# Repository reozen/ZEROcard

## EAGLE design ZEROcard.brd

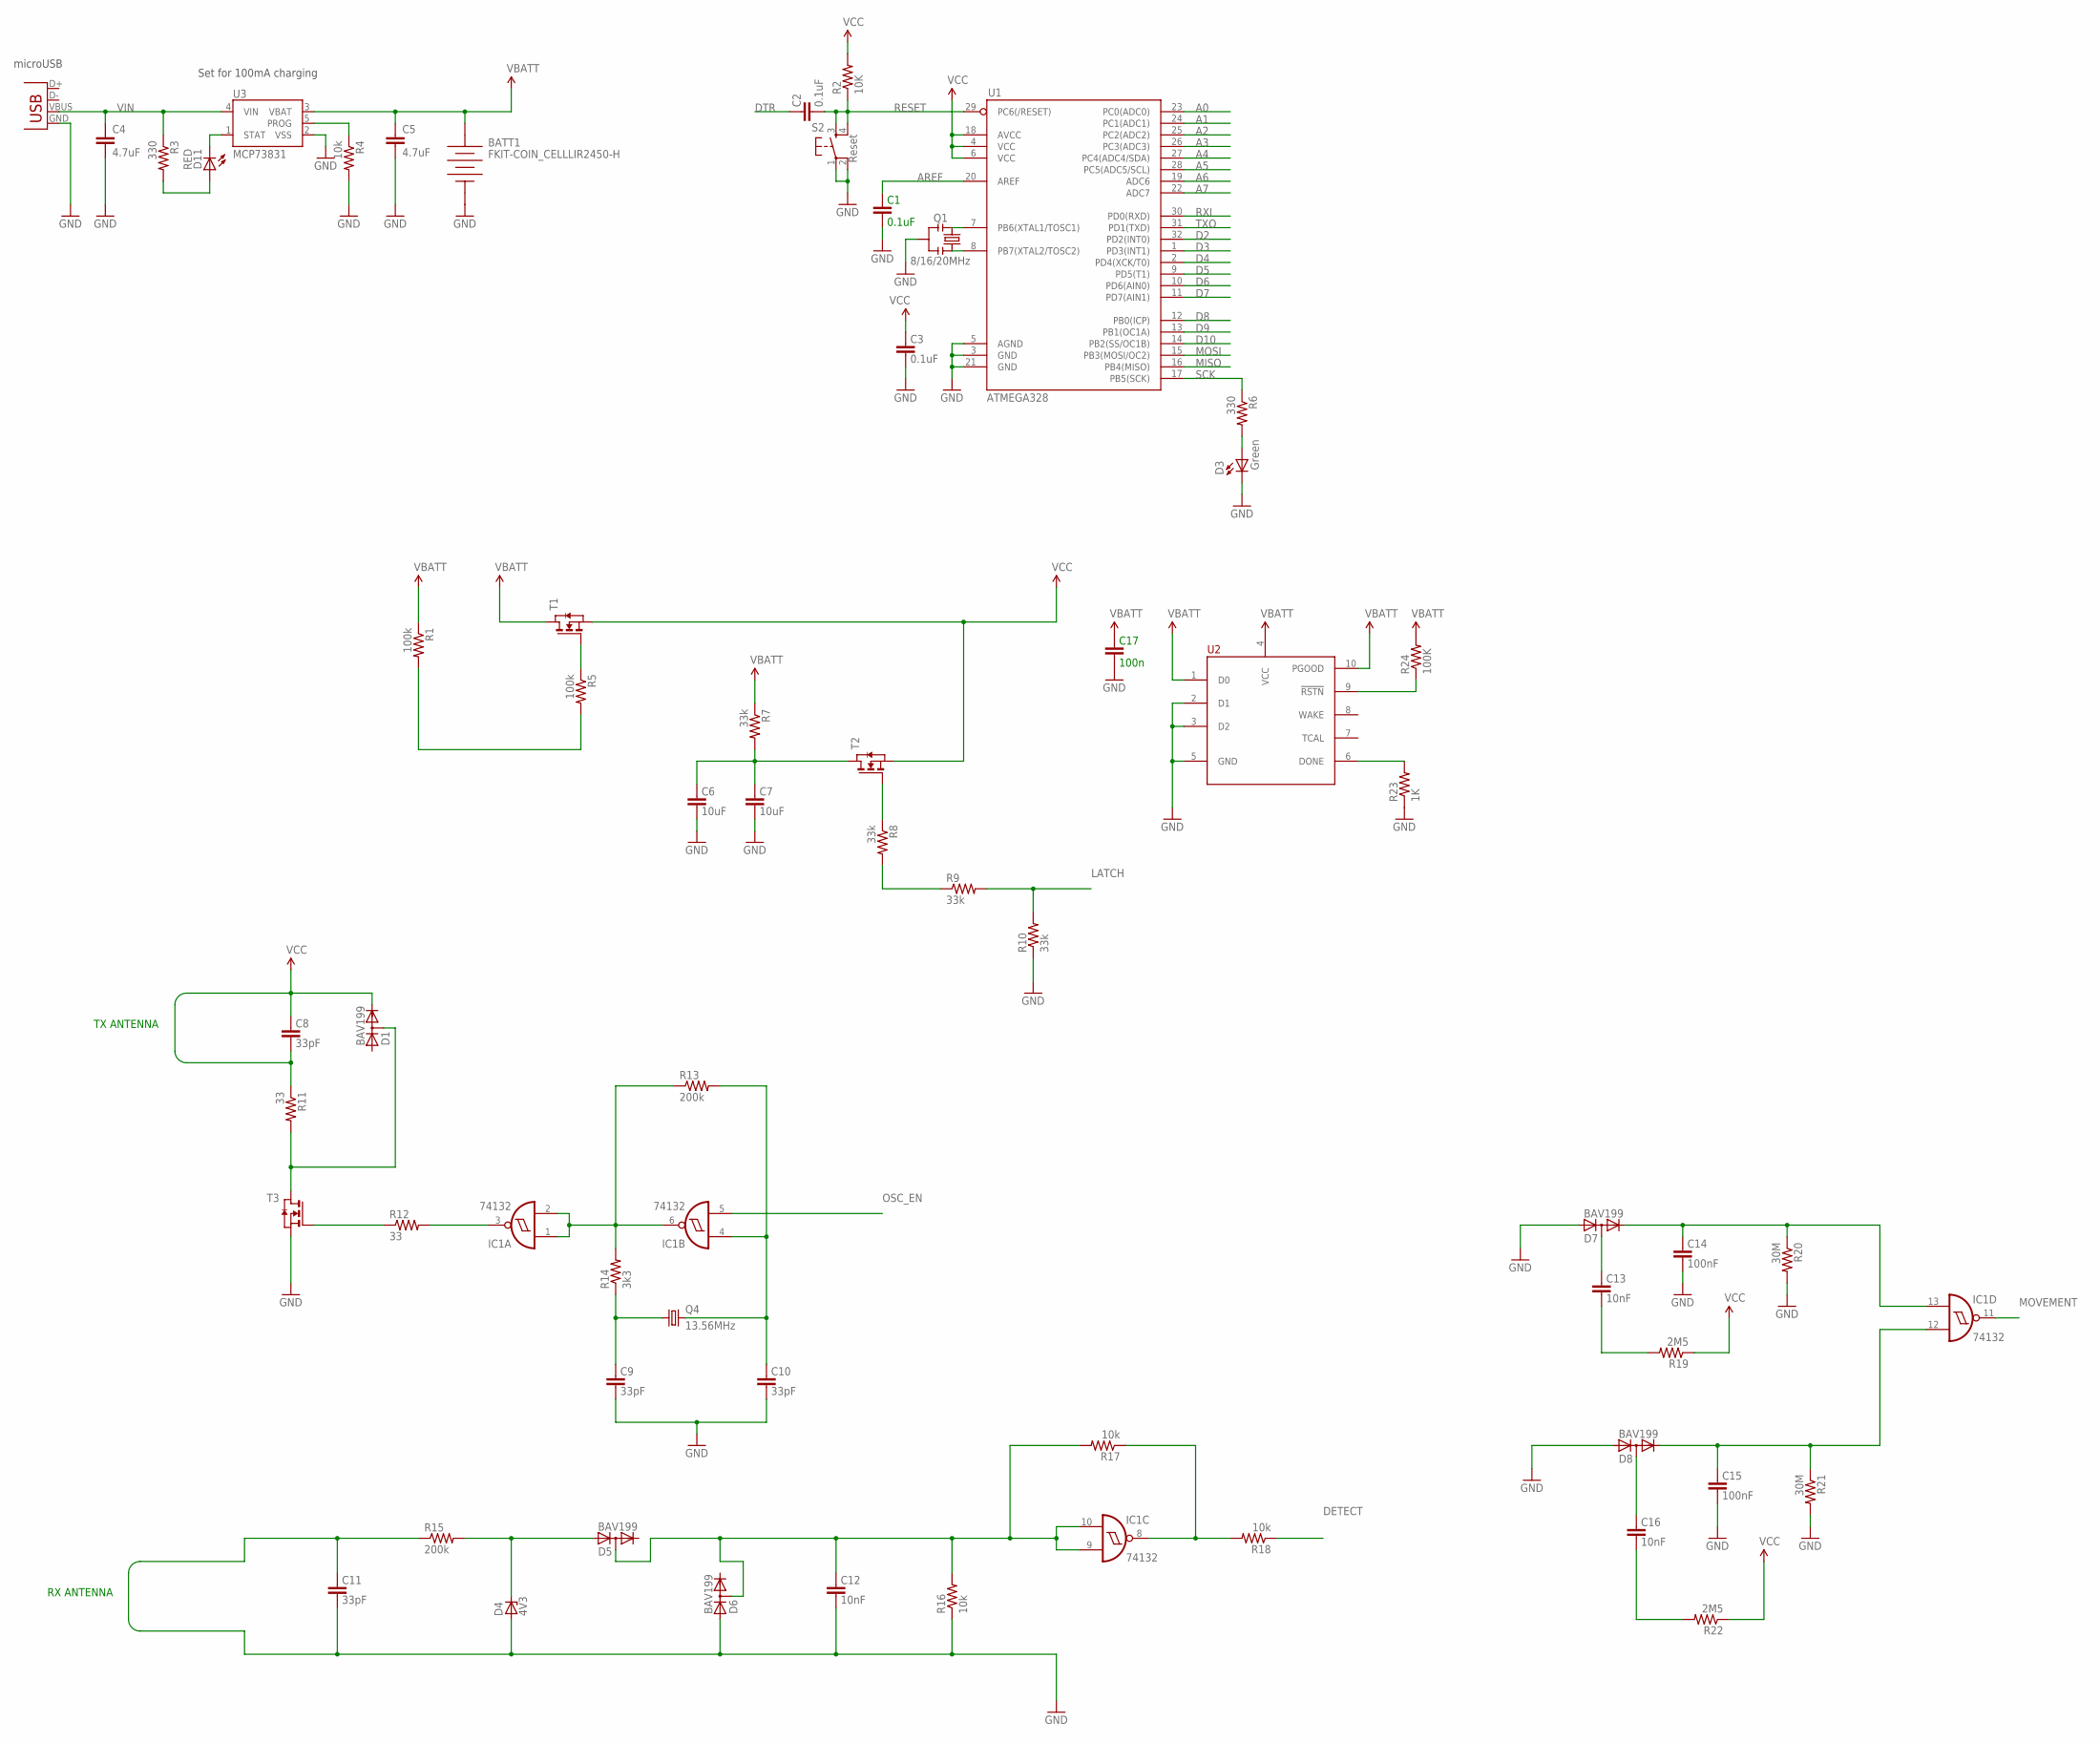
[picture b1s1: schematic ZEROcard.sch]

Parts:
BATT1: FKIT-COIN_CELLLIR2450-H; FKIT-LIR2450-H
C1, C2, C3: 0.1uF; 0805
C4, C5: 4.7uF; 0805
C6, C7: 10uF; 0805
C8, C9, C10, C11: 33pF; 0805
C12, C13, C16: 10nF; 0805
C14, C15: 100nF; 0805
C17: 100n; 0805
D1, D5, D6, D7, D8: BAV199; SOT23
D3: Green; LED-0603
D4: 4V3; SOT23
D11: RED; LED-0603
IC1: 74132; TSSOP14
Q1: 8/16/20MHz; RESONATOR-SMD
Q4: 13.56MHz; MC-306
R1, R5: 100k; 0805
R2: 10K; 0805
R3, R6: 330; 0805
R4, R16, R17, R18: 10k; 0805
R7, R8, R9, R10: 33k; 0805
R11, R12: 33; 0805
R13, R15: 200k; 0805
R14: 3k3; 0805
R19, R22: 2M5; 0805
R20, R21: 30M; 0805
R23: 1K; 0805
R24: 100K; 0805
S2: Reset; TACTILE_SWITCH_SMD
T1, T2, T3: NMOSSOT23; SOT-23
U1: ATMEGA328; TQFP32-08
U2: TPL5000; MSOP10
U3: MCP73831; SOT23-5
X1: Micro USB; USB-MICROB

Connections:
3.3V: BATT1.POS, C5.1, C8.1, C8.2, C17.2, D1.2 (C), R1.1, R7.1, R11.1, R19.1, R22.1, R24.2, T1.1 (D), T1.2 (S), T2.2 (S), U2.1 (D0), U2.4 (VCC), U2.10 (PGOOD), U3.3 (VBAT)
A0: U1.23 (PC0(ADC0))
A1: U1.24 (PC1(ADC1))
A2: U1.25 (PC2(ADC2))
A3: U1.26 (PC3(ADC3))
A4: U1.27 (PC4(ADC4/SDA))
A5: U1.28 (PC5(ADC5/SCL))
A6: U1.19 (ADC6)
A7: U1.22 (ADC7)
AREF: C1.2, U1.20 (AREF)
D2: U1.32 (PD2(INT0))
D3: U1.1 (PD3(INT1))
D4: U1.2 (PD4(XCK/T0))
D5: U1.9 (PD5(T1))
D6: U1.10 (PD6(AIN0))
D7: U1.11 (PD7(AIN1))
D8: U1.12 (PB0(ICP))
D9: U1.13 (PB1(OC1A))
D10: U1.14 (PB2(SS/OC1B))
DETECT: R18.1
DTR: C2.2
GND: BATT1.NEG, C1.1, C3.1, C4.2, C5.2, C6.1, C7.1, C9.1, C10.1, C14.1, C15.1, C17.1, D3.C, D7.1 (A), D8.1 (A), IC1.7 (GND), Q1.2, R4.2, R10.1, R20.2, R21.2, R23.1, S2.1, S2.2, T3.2 (S), U1.3 (GND), U1.5 (AGND), U1.21 (GND), U2.2 (D1), U2.3 (D2), U2.5 (GND), U3.2 (VSS), X1.GND
LATCH: R9.2, R10.2
MISO: U1.16 (PB4(MISO))
MOSI: U1.15 (PB3(MOSI/OC2))
MOVEMENT: IC1.11 (O)
unnamed: Q1.1, U1.8 (PB7(XTAL2/TOSC2))
unnamed: Q1.3, U1.7 (PB6(XTAL1/TOSC1))
unnamed: D11.A, R3.2
unnamed: R1.2, R5.2
unnamed: D3.A, R6.2
unnamed: R5.1, T1.3 (G)
unnamed: C6.2, C7.2, R7.2, T2.1 (D)
unnamed: R8.2, R9.1
unnamed: C9.2, Q4.1, R14.1
unnamed: R8.1, T2.3 (G)
unnamed: R23.2, U2.6 (DONE)
unnamed: D1.3 (AC), R11.2, T3.1 (D)
unnamed: D4.3 (C), D5.1 (A), R15.2
unnamed: R12.1, T3.3 (G)
unnamed: IC1.3 (O), R12.2
unnamed: IC1.1 (I0), IC1.2 (I1), IC1.6 (O), R13.1, R14.2
unnamed: C13.2, D7.3 (AC)
unnamed: C10.2, IC1.4 (I0), Q4.4 (2), R13.2
unnamed: C12.2, D5.3 (AC), D6.3 (AC), IC1.9 (I1), IC1.10 (I0), R16.2, R17.2
unnamed: C13.1, R19.2
unnamed: C14.2, D7.2 (C), IC1.13 (I0), R20.1
unnamed: IC1.8 (O), R17.1, R18.2
unnamed: C15.2, D8.2 (C), IC1.12 (I1), R21.1
unnamed: C16.2, D8.3 (AC)
unnamed: C16.1, R22.2
unnamed: R24.1, U2.9 (!RSTN)
OSC_EN: IC1.5 (I1)
PROG: R4.1, U3.5 (PROG)
RESET: C2.1, R2.1, S2.3, S2.4, U1.29 (PC6(/RESET))
RX: C11.1, C11.2, C12.1, D4.1 (A), D6.1 (A), R15.1, R16.1
RXI: U1.30 (PD0(RXD))
SCK: R6.1, U1.17 (PB5(SCK))
STAT: D11.C, U3.1 (STAT)
TXO: U1.31 (PD1(TXD))
VCC: C3.2, IC1.14 (VCC), R2.2, U1.4 (VCC), U1.6 (VCC), U1.18 (AVCC)
VIN: C4.1, R3.1, U3.4 (VIN), X1.VBUS

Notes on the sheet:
Set for 100mA charging
microUSB
TX ANTENNA
RX ANTENNA

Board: 2 copper layers, 61 parts (0 on the bottom side), 37 nets, no tracks yet.

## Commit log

2014-06-08 r2 release from Alberto

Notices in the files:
parts and their libraries:
SparkFun-Electromechanical: Licensing: Creative Commons ShareAlike 4.0 International - https://creativecommons.org/licenses/by-sa/4.0
